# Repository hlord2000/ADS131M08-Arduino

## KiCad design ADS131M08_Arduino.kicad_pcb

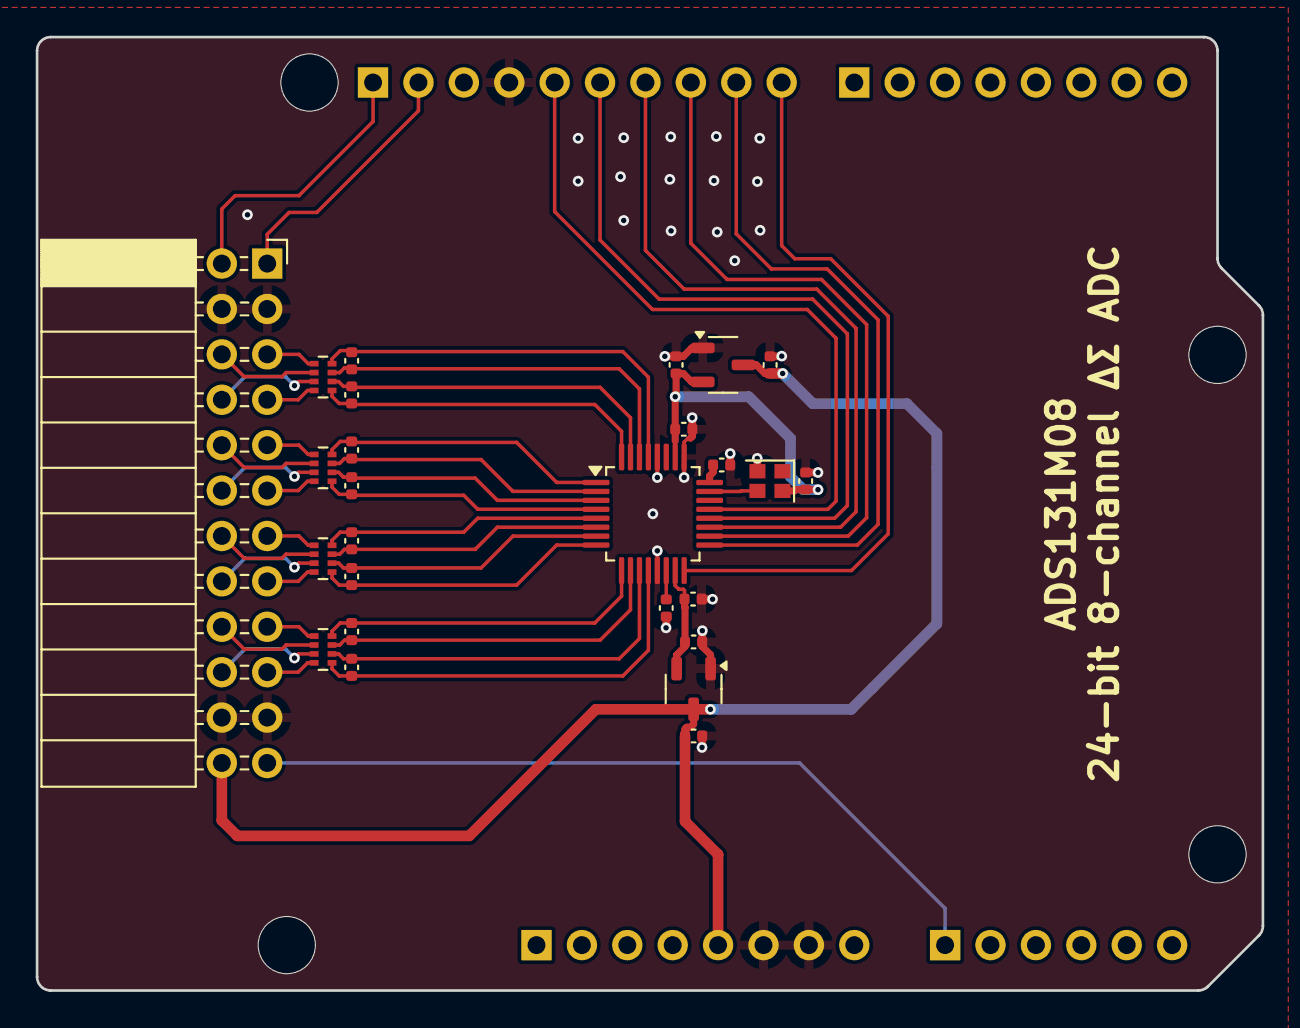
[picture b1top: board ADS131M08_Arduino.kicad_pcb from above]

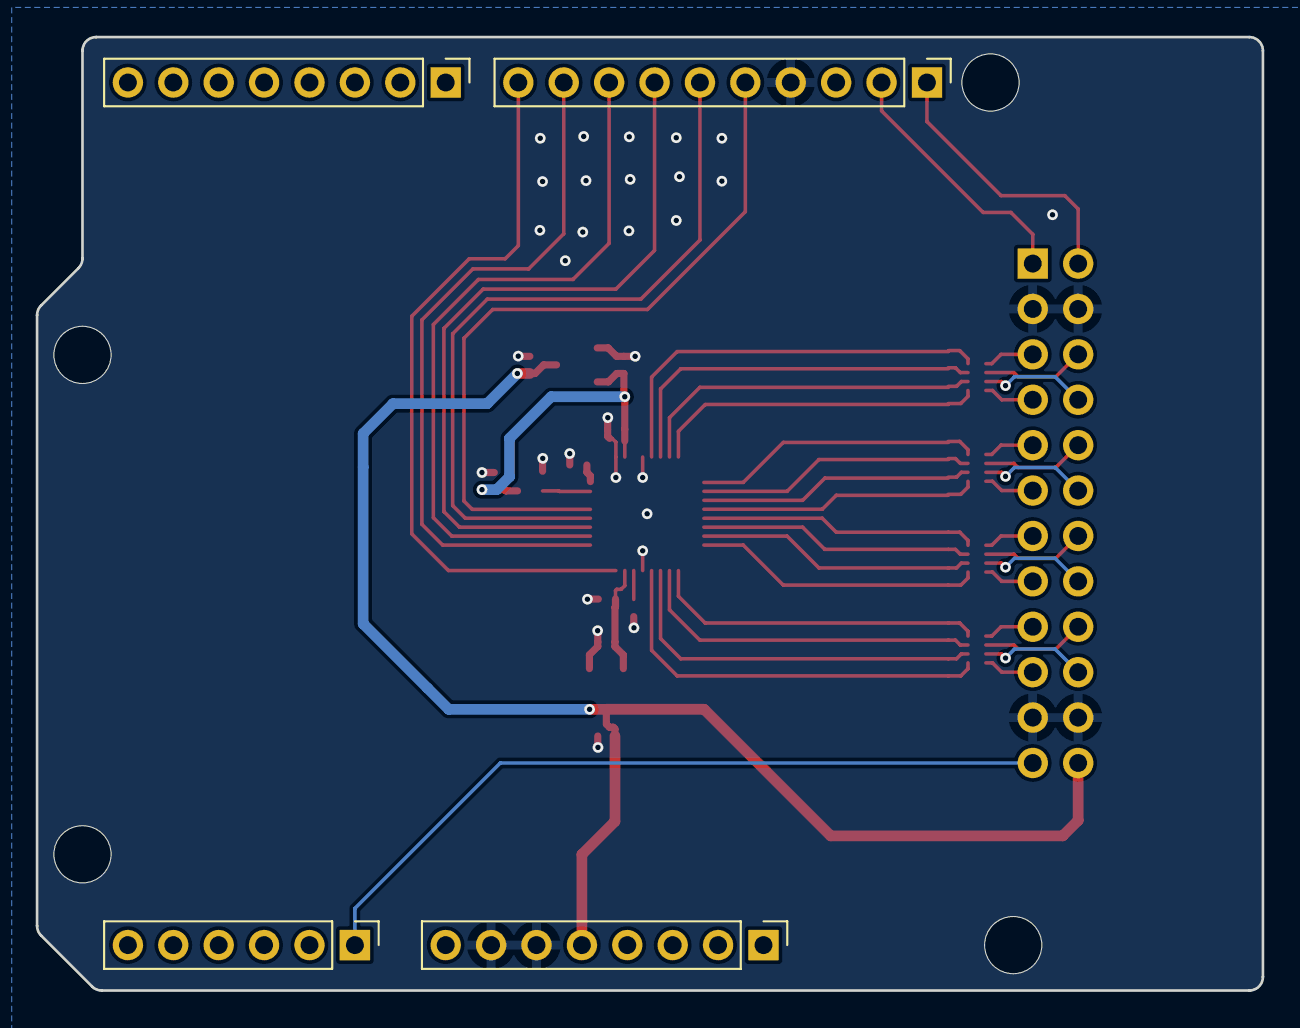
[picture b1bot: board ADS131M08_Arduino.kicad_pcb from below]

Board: 4 copper layers, 68.6 x 53.3 mm, 34 parts (4 on the bottom side), 48 nets.

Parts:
C1, C2, C14, C15, C16, C17: 1uF; C_0402_1005Metric
C3, C5: 100nF; C_0402_1005Metric
C4: 220nF; C_0402_1005Metric
C6, C7, C8, C9, C10, C11, C12, C13: 10nF; C_0402_1005Metric
J1: Power; PinHeader_1x08_P2.54mm_Vertical
J2: Digital/PWM; PinHeader_1x10_P2.54mm_Vertical
J3: Analog; PinHeader_1x06_P2.54mm_Vertical
J4: Digital/PWM; PinHeader_1x08_P2.54mm_Vertical
J5: Conn_02x12_Odd_Even; PinSocket_2x12_P2.54mm_Horizontal
MH1, MH2, MH3, MH4: MountingHole_3.2mm
RN1, RN2, RN3, RN4: 10kR; R_Array_Concave_4x0402
U1: ADS131M08IPB; LQFP-32_5x5mm_P0.5mm
U2, U3: XC6206PxxxMR; SOT-23-3
X1: SiT8008; Crystal_SMD_2016-4Pin_2.0x1.6mm

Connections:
+3.3V: C1.1, C5.1, C15.1, U1.26 (DVDD), U2.2 (VO), X1.4 (VDD)
+3.3VADC: C2.1, C17.1, U1.15 (AVDD), U3.2 (VO)
+5V: C14.1, C16.1, J1.5, J5.24, U2.3 (VI), U3.3 (VI)
/8: J2.10, U1.16 (~RESET/~SYNC)
/12: J2.6, U1.20 (DOUT)
/13: J2.5, U1.21 (DIN)
/*9: J2.9, U1.17 (~CS)
/*10: J2.8, U1.18 (~DRDY)
/*11: J2.7, U1.19 (SCLK)
/A0: J3.1, J5.23
/AIN0N: C6.2, RN3.3 (R3.1), U1.30 (AIN0N)
/AIN0P: C6.1, RN3.4 (R4.1), U1.29 (AIN0P)
/AIN1N: C7.2, RN3.2 (R2.1), U1.31 (AIN1N)
/AIN1P: C7.1, RN3.1 (R1.1), U1.32 (AIN1P)
/AIN2N: C8.2, RN1.3 (R3.1), U1.2 (AIN2N)
/AIN2P: C8.1, RN1.4 (R4.1), U1.1 (AIN2P)
/AIN3N: C9.2, RN1.2 (R2.1), U1.3 (AIN3N)
/AIN3P: C9.1, RN1.1 (R1.1), U1.4 (AIN3P)
/AIN4N: C10.2, RN2.3 (R3.1), U1.6 (AIN4N)
/AIN4P: C10.1, RN2.4 (R4.1), U1.5 (AIN4P)
/AIN5N: C11.2, RN2.2 (R2.1), U1.7 (AIN5N)
/AIN5P: C11.1, RN2.1 (R1.1), U1.8 (AIN5P)
/AIN6N: C12.2, RN4.3 (R3.1), U1.10 (AIN6N)
/AIN6P: C12.1, RN4.4 (R4.1), U1.9 (AIN6P)
/AIN7N: C13.2, RN4.2 (R2.1), U1.11 (AIN7N)
/AIN7P: C13.1, RN4.1 (R1.1), U1.12 (AIN7P)
/IN0+: J5.5, RN3.5 (R4.2)
/IN0-: J5.6, RN3.6 (R3.2)
/IN1+: J5.8, RN3.7 (R2.2)
/IN1-: J5.7, RN3.8 (R1.2)
/IN2+: J5.9, RN1.5 (R4.2)
/IN2-: J5.10, RN1.6 (R3.2)
/IN3+: J5.12, RN1.7 (R2.2)
/IN3-: J5.11, RN1.8 (R1.2)
/IN4+: J5.13, RN2.5 (R4.2)
/IN4-: J5.14, RN2.6 (R3.2)
/IN5+: J5.16, RN2.7 (R2.2)
/IN5-: J5.15, RN2.8 (R1.2)
/IN6+: J5.17, RN4.5 (R4.2)
/IN6-: J5.18, RN4.6 (R3.2)
/IN7+: J5.20, RN4.7 (R2.2)
/IN7-: J5.19, RN4.8 (R1.2)
/SCL/A5: J2.1, J5.2
/SDA/A4: J2.2, J5.1
GND: C1.2, C2.2, C3.2, C4.2, C5.2, C14.2, C15.2, C16.2, C17.2, J1.6, J1.7, J2.4, J5.3, J5.4, J5.21, J5.22, U1.13 (GND), U1.25 (DGND), U1.28 (AGND), U2.1 (GND), U3.1 (GND), X1.2 (GND)
unnamed: C4.1, U1.24 (CAP)
unnamed: C3.1, U1.14 (REFIN)
unnamed: U1.23 (XTAL1/CLKIN), X1.3 (OUT)

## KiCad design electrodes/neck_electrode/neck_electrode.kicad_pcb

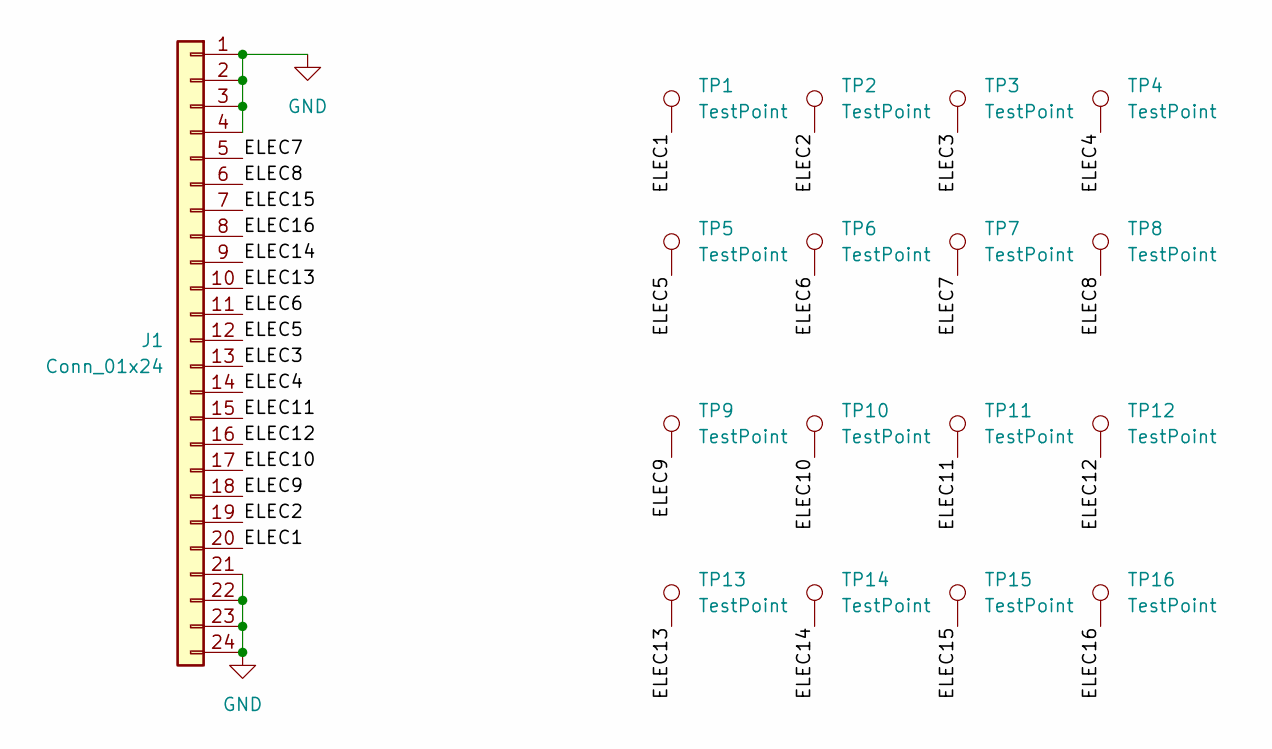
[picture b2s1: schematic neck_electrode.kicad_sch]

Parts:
J1: Conn_01x24; FPC-1x24_P0.5mm_W8.5mm_H1.0mm
TP1, TP2, TP3, TP4, TP5, TP6, TP7, TP8, TP9, TP10, TP11, TP12, TP13, TP14, TP15, TP16: TestPoint; S70-332002045R

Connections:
/ELEC1: J1.20, TP1.1
/ELEC2: J1.19, TP2.1
/ELEC3: J1.13, TP3.1
/ELEC4: J1.14, TP4.1
/ELEC5: J1.12, TP5.1
/ELEC6: J1.11, TP6.1
/ELEC7: J1.5, TP7.1
/ELEC8: J1.6, TP8.1
/ELEC9: J1.18, TP9.1
/ELEC10: J1.17, TP10.1
/ELEC11: J1.15, TP11.1
/ELEC12: J1.16, TP12.1
/ELEC13: J1.10, TP13.1
/ELEC14: J1.9, TP14.1
/ELEC15: J1.7, TP15.1
/ELEC16: J1.8, TP16.1
GND: J1.1, J1.2, J1.3, J1.4, J1.21, J1.22, J1.23, J1.24

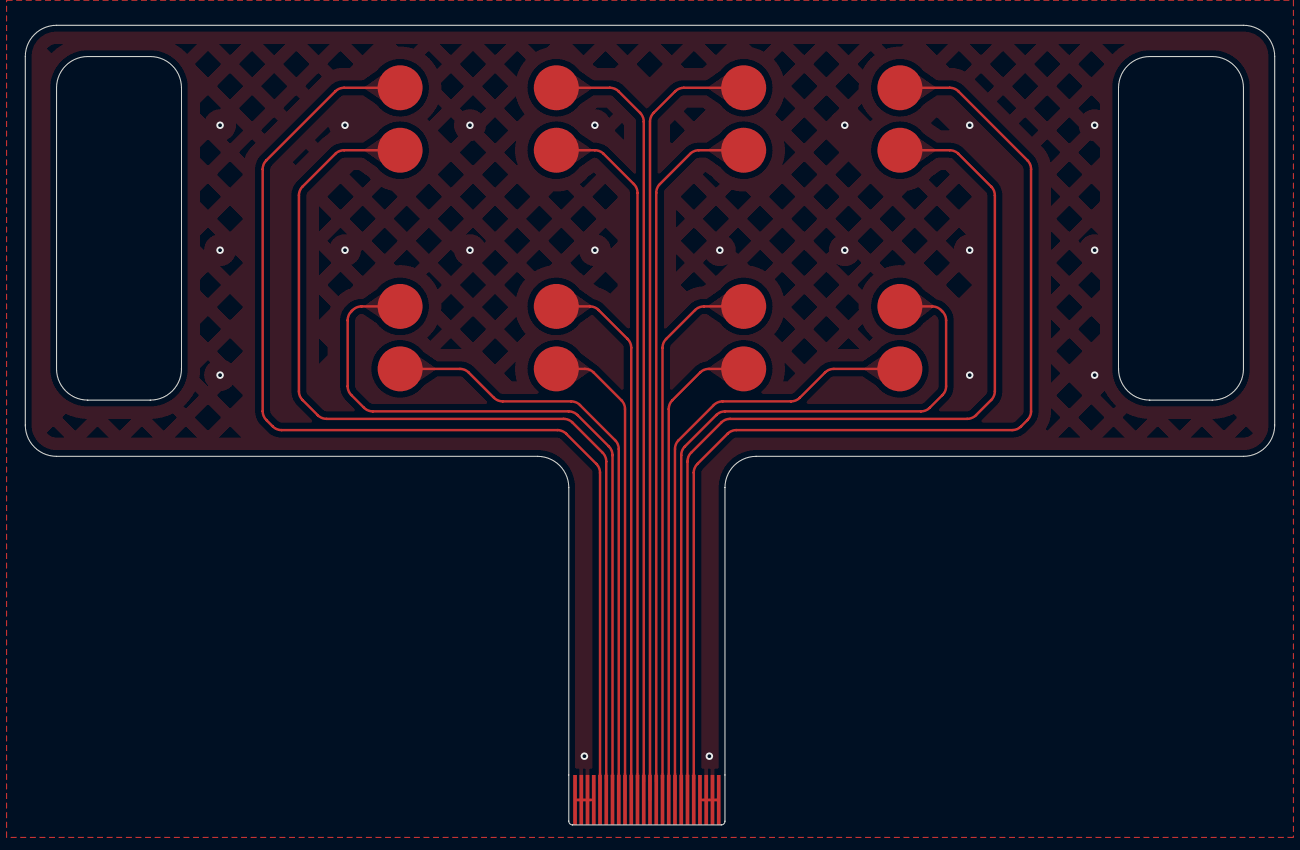
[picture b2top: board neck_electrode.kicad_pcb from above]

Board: 2 copper layers, 100.0 x 64.0 mm, 17 parts (0 on the bottom side), 17 nets.

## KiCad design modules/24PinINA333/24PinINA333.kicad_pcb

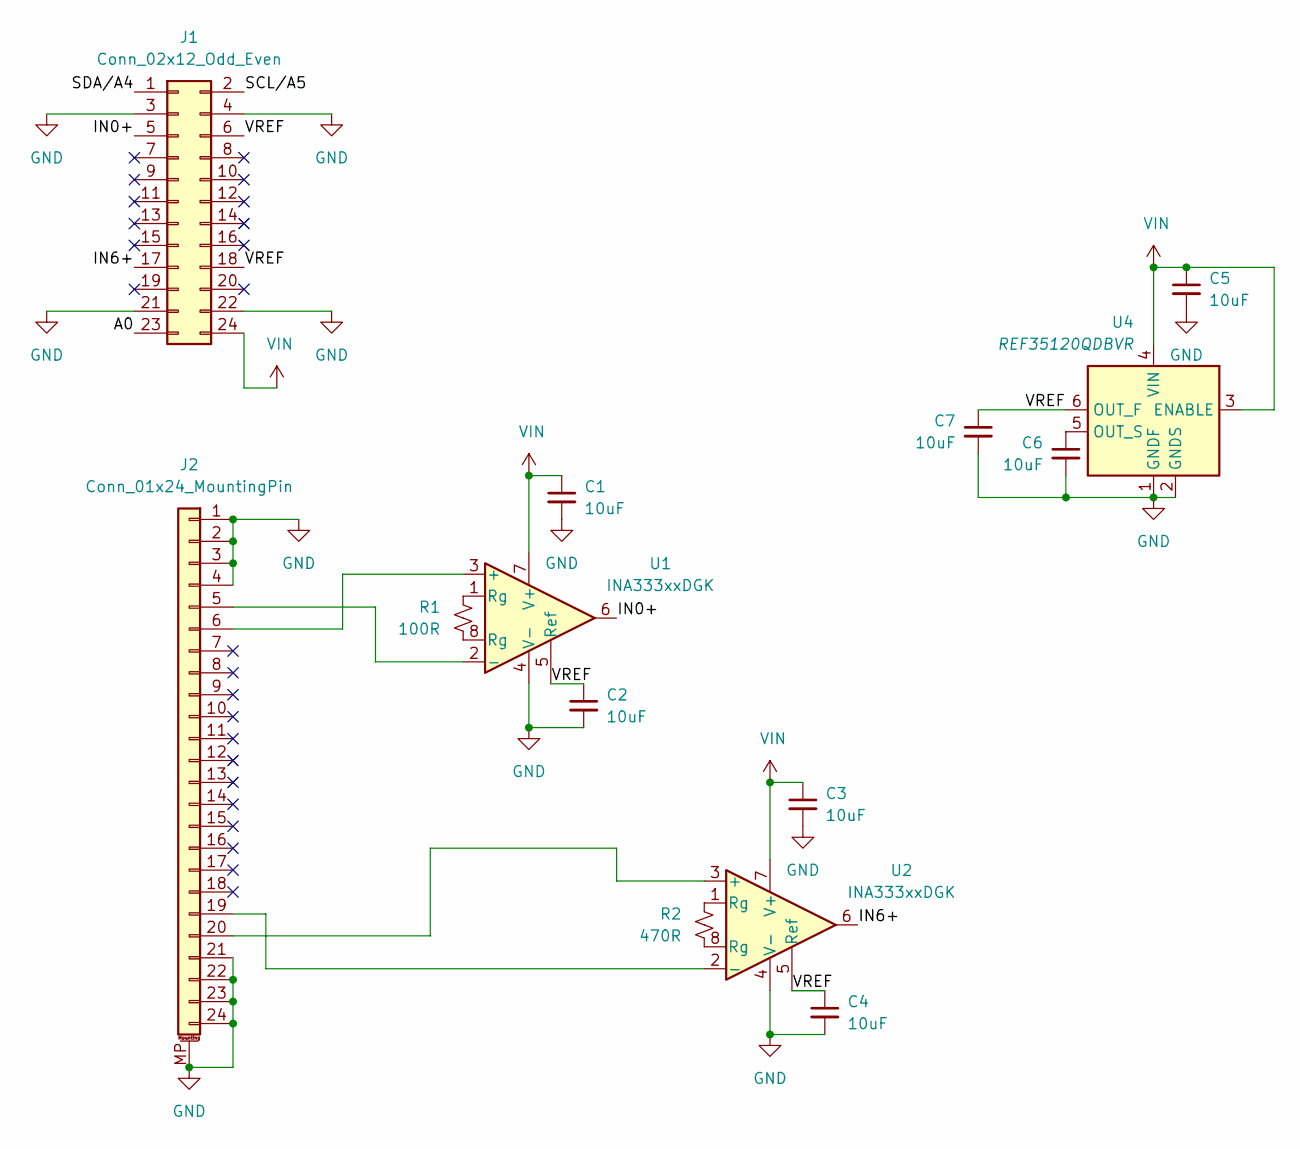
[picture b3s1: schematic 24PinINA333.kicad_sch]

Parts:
C1, C2, C3, C4, C5, C6, C7: 10uF; C_0603_1608Metric; LCSC C96446
J1: Conn_02x12_Odd_Even; PinHeader_2x12_P2.54mm_Horizontal; LCSC C5383094
J2: Conn_01x24_MountingPin; 0.5K-AS-24PWB_1x24-1MP_P0.5mm_Horizontal
R1: 100R; R_1206_3216Metric; LCSC C17901
R2: 470R; R_0603_1608Metric; LCSC C23179
U1, U2: INA333xxDGK; VSSOP-8_3x3mm_P0.65mm; LCSC C19450
U4: REF35120QDBVR; SOT-23-6; LCSC C5722646

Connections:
/A0: J1.23
/IN0+: J1.5, U1.6
/IN6+: J1.17, U2.6
/SCL/A5: J1.2
/SDA/A4: J1.1
/VREF: C2.1, C4.1, C7.1, J1.6, J1.18, U1.5 (Ref), U2.5 (Ref), U4.6 (OUT_F)
GND: C1.2, C2.2, C3.2, C4.2, C5.2, C6.2, C7.2, J1.3, J1.4, J1.21, J1.22, J2.1, J2.2, J2.3, J2.4, J2.21, J2.22, J2.23, J2.24, J2.MP (MountPin), U1.4 (V-), U2.4 (V-), U4.1 (GNDF), U4.2 (GNDS)
unnamed: J2.5, U1.2 (-)
unnamed: J2.6, U1.3 (+)
unnamed: J2.19, U2.2 (-)
unnamed: J2.20, U2.3 (+)
unnamed: R1.1, U1.1 (Rg)
unnamed: R1.2, U1.8 (Rg)
unnamed: R2.1, U2.1 (Rg)
unnamed: R2.2, U2.8 (Rg)
unnamed: C6.1, U4.5 (OUT_S)
VIN: C1.1, C3.1, C5.1, J1.24, U1.7 (V+), U2.7 (V+), U4.3 (ENABLE), U4.4 (VIN)

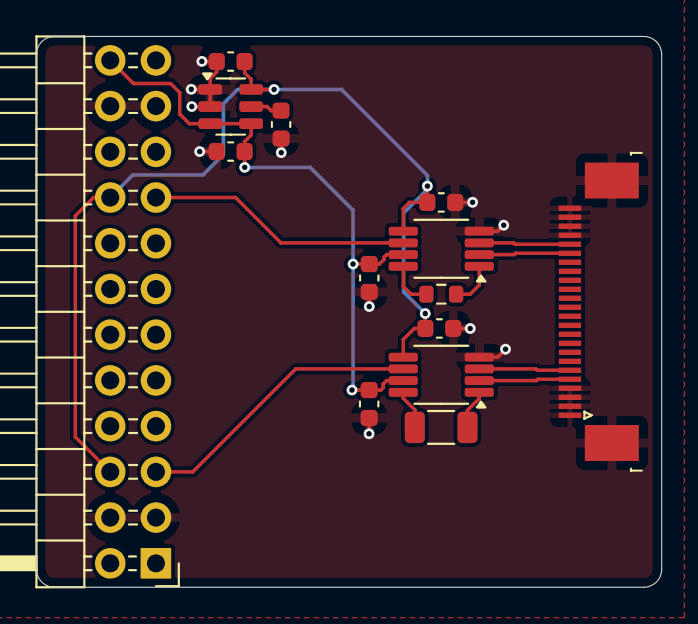
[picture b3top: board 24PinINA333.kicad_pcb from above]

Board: 4 copper layers, 34.7 x 30.6 mm, 14 parts (0 on the bottom side), 14 nets.

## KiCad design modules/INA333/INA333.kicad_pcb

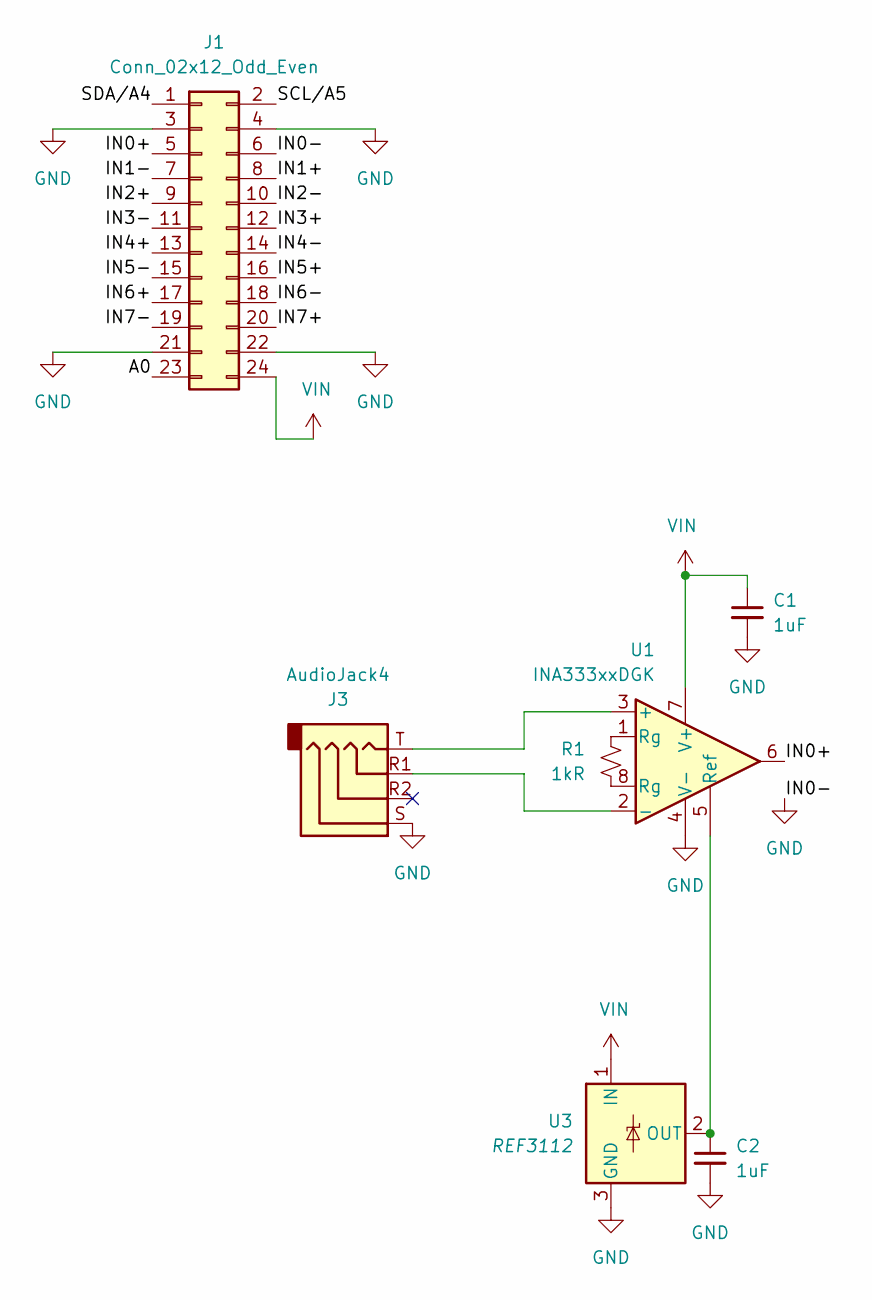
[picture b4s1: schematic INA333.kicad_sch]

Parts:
C1, C2: 1uF; C_0402_1005Metric; LCSC C15849
J1: Conn_02x12_Odd_Even; PinHeader_2x12_P2.54mm_Horizontal; LCSC C5383094
J3: AudioJack4; Jack_3.5mm_PJ320D_Horizontal; LCSC C431535
R1: 1kR; R_0402_1005Metric_Pad0.72x0.64mm_HandSolder; LCSC C11702
U1: INA333xxDGK; VSSOP-8_3x3mm_P0.65mm; LCSC C19450
U3: REF3112; SOT-23; LCSC C74223

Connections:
/A0: J1.23
/IN0+: J1.5, U1.6
/IN1+: J1.8
/IN1-: J1.7
/IN2+: J1.9
/IN2-: J1.10
/IN3+: J1.12
/IN3-: J1.11
/IN4+: J1.13
/IN4-: J1.14
/IN5+: J1.16
/IN5-: J1.15
/IN6+: J1.17
/IN6-: J1.18
/IN7+: J1.20
/IN7-: J1.19
/SCL/A5: J1.2
/SDA/A4: J1.1
GND: C1.2, C2.2, J1.3, J1.4, J1.6, J1.21, J1.22, J3.S, U1.4 (V-), U3.3 (GND)
unnamed: R1.1, U1.1 (Rg)
unnamed: R1.2, U1.8 (Rg)
unnamed: J3.T, U1.3 (+)
unnamed: J3.R1, U1.2 (-)
unnamed: C2.1, U1.5 (Ref), U3.2 (OUT)
VIN: C1.1, J1.24, U1.7 (V+), U3.1 (IN)

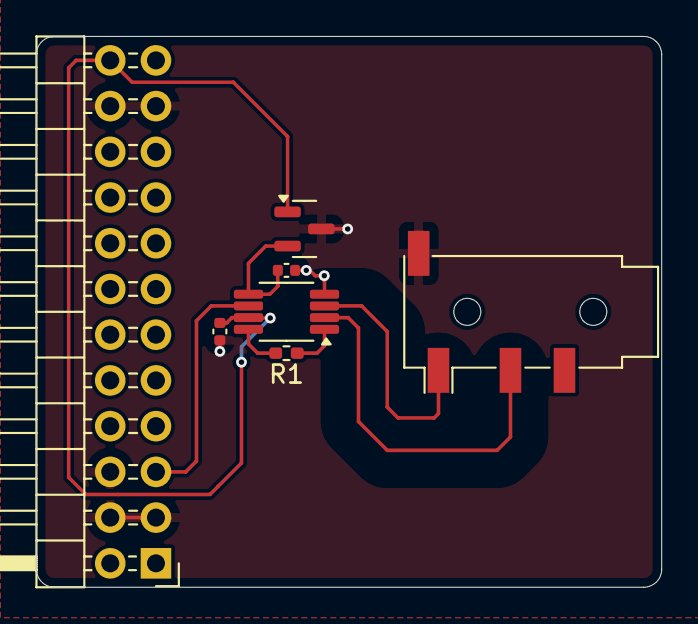
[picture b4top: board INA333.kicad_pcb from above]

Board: 2 copper layers, 34.7 x 30.6 mm, 7 parts (0 on the bottom side), 8 nets.

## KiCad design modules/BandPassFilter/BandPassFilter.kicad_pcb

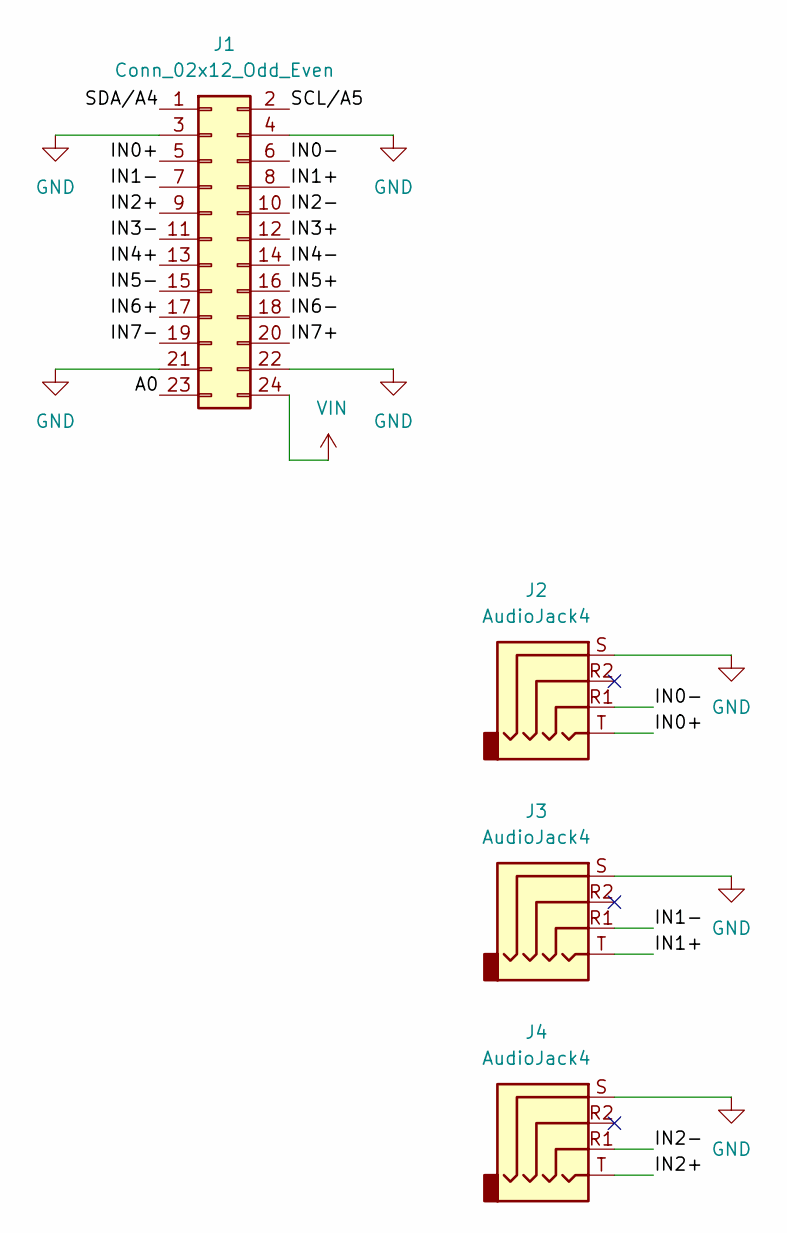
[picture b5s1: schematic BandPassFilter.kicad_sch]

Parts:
J1: Conn_02x12_Odd_Even; PinHeader_2x12_P2.54mm_Horizontal; LCSC C5383094
J2, J3, J4: AudioJack4; Jack_3.5mm_PJ320D_Horizontal; LCSC C431535

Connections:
/A0: J1.23
/IN0+: J1.5, J2.T
/IN0-: J1.6, J2.R1
/IN1+: J1.8, J3.T
/IN1-: J1.7, J3.R1
/IN2+: J1.9, J4.T
/IN2-: J1.10, J4.R1
/IN3+: J1.12
/IN3-: J1.11
/IN4+: J1.13
/IN4-: J1.14
/IN5+: J1.16
/IN5-: J1.15
/IN6+: J1.17
/IN6-: J1.18
/IN7+: J1.20
/IN7-: J1.19
/SCL/A5: J1.2
/SDA/A4: J1.1
GND: J1.3, J1.4, J1.21, J1.22, J2.S, J3.S, J4.S
VIN: J1.24

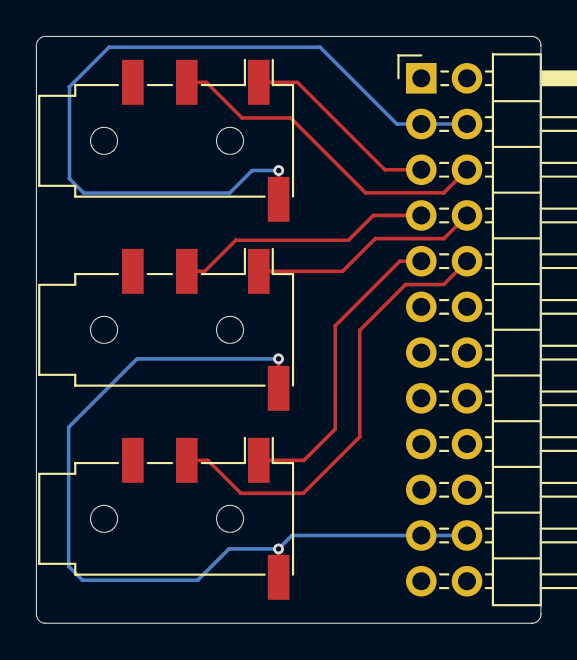
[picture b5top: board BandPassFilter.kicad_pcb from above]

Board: 2 copper layers, 28.0 x 32.6 mm, 4 parts (0 on the bottom side), 7 nets.

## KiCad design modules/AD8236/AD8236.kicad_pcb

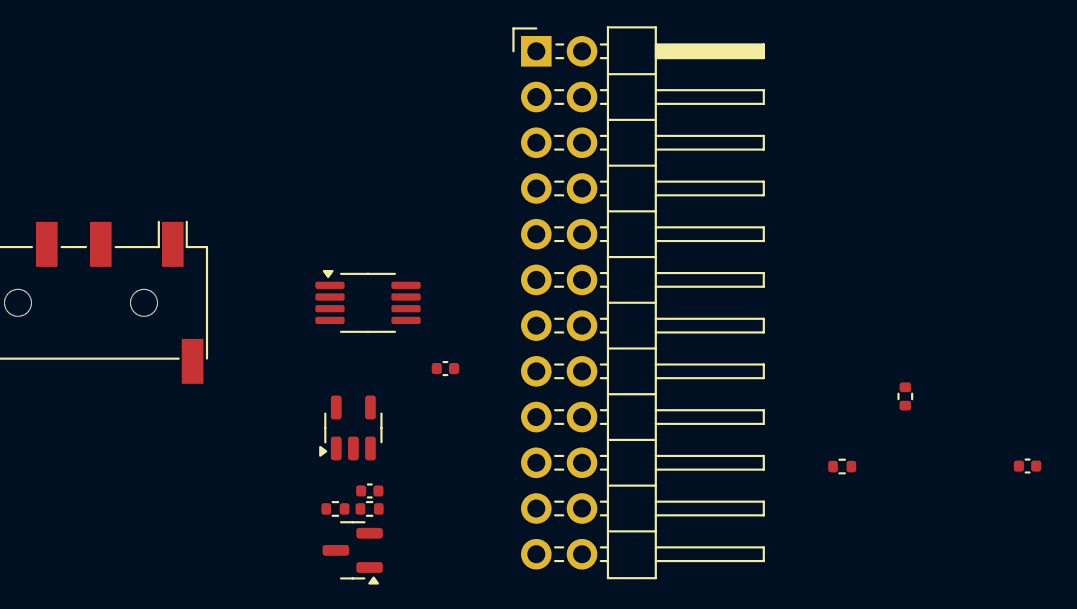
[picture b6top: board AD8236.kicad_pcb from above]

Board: 2 copper layers, 12 parts (0 on the bottom side), 9 nets, no tracks yet.

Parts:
C1, C2, C3: 1uF; C_0402_1005Metric
J1: Conn_02x12_Odd_Even; PinHeader_2x12_P2.54mm_Horizontal
J2: AudioJack4; Jack_3.5mm_PJ320D_Horizontal
R2, R3, R4, R5: 100kR; R_0402_1005Metric
U1: AD8236ARMZ; MSOP-8_3x3mm_P0.65mm
U2: AD8603; TSOT-23-5
U3: REF3012; SOT-23

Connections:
/IN0+: J1.5, U1.7
/RST: J1.1, R2.2, R3.2
GND: C1.2, C2.2, C3.2, J1.3, J1.4, J1.6, J1.21, J1.22, J2.S, R2.1, R3.1, R5.2, U1.5 (Vs-), U2.2 (V-), U3.3 (GND)
unnamed: J2.R1, U1.4 (+)
unnamed: J2.T, U1.1 (-)
unnamed: U1.6 (Ref), U2.1, U2.4 (-)
unnamed: R4.2, R5.1, U2.3 (+)
unnamed: C3.1, R4.1, U3.2 (OUT)
VIN: C1.1, C2.1, J1.24, U1.8 (Vs+), U2.5 (V+), U3.1 (IN)

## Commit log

2024-08-03 Updated to use resistor arrays
2024-11-09 Commit nov 9 2024
